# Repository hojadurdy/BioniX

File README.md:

### BioniX
Controller board for a prototype robotic prosthetic hand. 

#Features

- 5 servo motors. 1 for each finger.
- 2 servo motors for wrist gimbal.
- Onboard accelerometer and gyro.
- nRF805 Bleetooth SoC to communicate with mobile app.
- 600mA Li-Ion battery charging.
- 3.3V@1A Buck-Boost converter for EMG sensor and for the rest of the board.
- 6V@4A Boost converter for servos.

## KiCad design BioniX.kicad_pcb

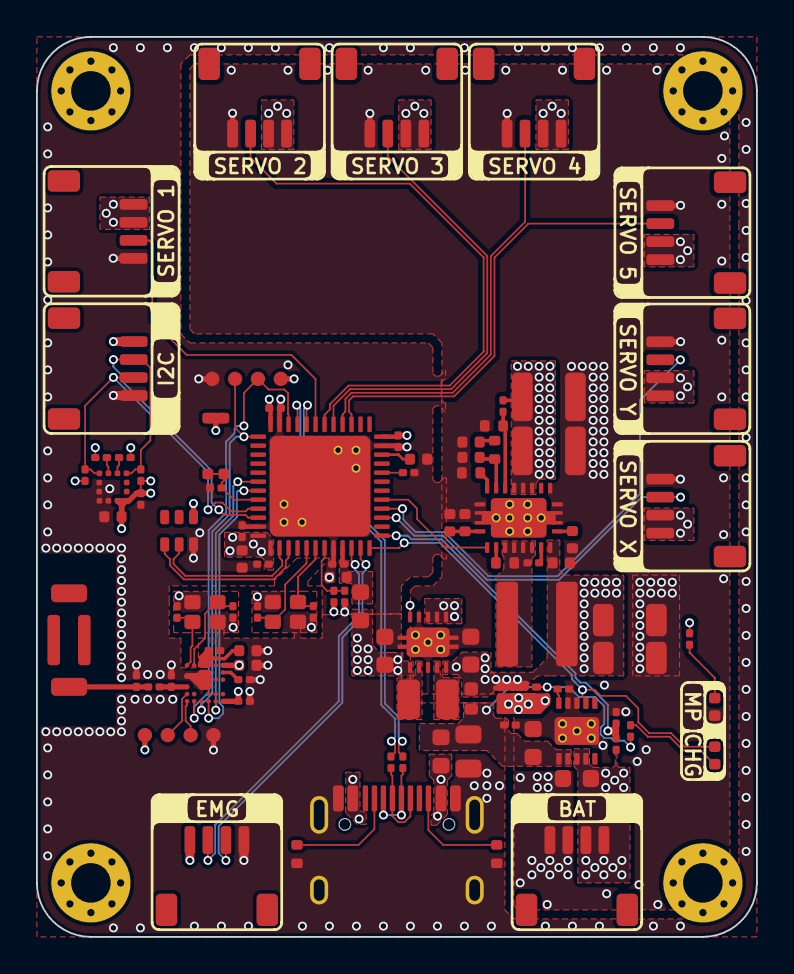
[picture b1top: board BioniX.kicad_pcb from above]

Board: 4 copper layers, 40.0 x 50.0 mm, 97 parts (0 on the bottom side), 64 nets.

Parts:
ANT1: 2450AT42B100; 2450AT42B100E
C1: 10uF; C_0805_2012Metric
C10, C60: 10uF; C_0402_1005Metric
C11, C12, C13, C14, C15, C18, C22, C24, C28, C52, C61: 100nF; C_0201_0603Metric
C16, C23, C54, C55: 1uF; C_0402_1005Metric
C17, C27: 2.2uF; C_0402_1005Metric
C19, C20, C21, C110: 18pF; C_0201_0603Metric
C25, C26: TBD; C_0201_0603Metric
C30, C31, C40: 10uF; C_0603_1608Metric
C41: 22uF; C_0603_1608Metric
C50, C51: 10uF; C_1206_3216Metric
C53: 100nF; C_0402_1005Metric
C56: 8.2nF; C_0402_1005Metric
C57: 560pF; C_0402_1005Metric
C58: 30pF; C_0402_1005Metric
C59, C510: 47uF; C_1210_3225Metric
D2: CCS15S30; CST2C
D3: APA102-2020
D30: STAT; LED_0402_1005Metric
D50: MOTOR_PWR; LED_0402_1005Metric
F1: 1A; Fuse_0603_1608Metric
FB1: 100@100MHz; L_0603_1608Metric
H1, H2, H3, H4: MountingHole; MountingHole_2.2mm_M2_Pad_Via
J1: USB-C; USB2.0_Type-C_Connector
J3: BAT; JST_SH_SM04B-SRSS-TB_1x04-1MP_P1.00mm_Horizontal
J4: EMG; JST_SH_SM04B-SRSS-TB_1x04-1MP_P1.00mm_Horizontal
J5: I2C; JST_SH_SM04B-SRSS-TB_1x04-1MP_P1.00mm_Horizontal
J6: Servo_X; JST_SH_SM04B-SRSS-TB_1x04-1MP_P1.00mm_Horizontal
J7: Servo_Y; JST_SH_SM04B-SRSS-TB_1x04-1MP_P1.00mm_Horizontal
J8, J9: SWD; SWD_Pogo_Pad
J10: Servo_1; JST_SH_SM04B-SRSS-TB_1x04-1MP_P1.00mm_Horizontal
J11: Servo_2; JST_SH_SM04B-SRSS-TB_1x04-1MP_P1.00mm_Horizontal
J12: Servo_3; JST_SH_SM04B-SRSS-TB_1x04-1MP_P1.00mm_Horizontal
J13: Servo_4; JST_SH_SM04B-SRSS-TB_1x04-1MP_P1.00mm_Horizontal
J14: Servo_5; JST_SH_SM04B-SRSS-TB_1x04-1MP_P1.00mm_Horizontal
L2: TBD; L_0201_0603Metric
L4: 1.5uH; L_1008_2520Metric
L5: 800nH; L_Coilcraft_XAL5030
Q1: SSM6J505NU; UDFN2020-6
R1, R2: 10; R_0201_0603Metric
R3, R4: 5.1K; R_0402_1005Metric
R5, R32, R33: 100K; R_0201_0603Metric
R10, R11, R12, R60, R61, R62, R63: 10K; R_0201_0603Metric
R30: 2.2K; R_0201_0603Metric
R31: 1.96K; R_0201_0603Metric
R50: 261K; R_0402_1005Metric
R51: 105K; R_0402_1005Metric
R52: 44.2K; R_0402_1005Metric
R53: 470K; R_0201_0603Metric
R54: 118K; R_0402_1005Metric
R55: 4.7K; R_0201_0603Metric
SW1: BOOT0; MicroSwitch
U1: STM32F411CEU6; QFN-48-1EP_7x7mm_P0.5mm_EP5.6x5.6mm
U2: nRF52805-CAAA; NRF52805-CAAA
U3: MCP73113-16SI; DFN-10-1EP_3x3mm_P0.5mm_EP1.55x2.48mm
U4: TPS63001DRC; Texas_VSON-10_3x3mm_P0.5mm
U5: TPS61088RHL; Texas_VQFN-RHL-20
U6: LIS2DW12TR; LGA-12_2x2mm_P0.5mm
Y1: 25MHz; Crystal_SMD_2016-4Pin_2.0x1.6mm
Y2: 32MHz; Crystal_SMD_2016-4Pin_2.0x1.6mm

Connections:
3.3V: C10.1, C11.1, C12.1, C13.1, C14.1, C27.1, C28.1, C41.1, C60.1, C61.1, D3.4 (VDD), FB1.2, J4.1 (VCC), J5.1 (VCC), J8.1 (VCC), J9.1 (VCC), R12.2, R60.2, R61.2, R62.2, R63.2, SW1.2, U1.1 (VBAT), U1.24 (VDD), U1.36 (VDD), U1.48 (VDD), U2.A6 (VDD), U2.G6 (VDD), U4.1 (VOUT), U4.10 (FB), U6.9 (VDD), U6.10 (VDD_IO)
6V: C59.1, C510.1, J6.1, J6.2, J7.1, J7.2, J10.1, J10.2, J11.1, J11.2, J12.1, J12.2, J13.1, J13.2, J14.1, J14.2, R53.1, R55.2, U5.14 (VOUT), U5.15 (VOUT), U5.16 (VOUT)
+3.3VA: C15.1, C16.1, FB1.1, U1.9 (VDDA)
BAT_STAT: D30.1 (K), U1.12 (PA2), U3.7 (STAT)
BAT_VOLT: R32.1, R33.2, U1.13 (PA3)
BOOST_EN: U1.17 (PA7), U5.2 (EN)
BOOT0: R10.2, SW1.1, U1.44 (BOOT0)
BT_1: J9.2 (DIO), U1.34 (PA13), U2.G2 (P0.21/NRESET)
BT_2: J9.3 (CLK), U1.37 (PA14), U2.G3 (P0.18)
BT_RX: U1.42 (PB6), U2.G5 (P0.12)
BT_SWCLK: J8.3 (CLK), U2.G1 (SWCLK)
BT_SWDIO: J8.2 (DIO), U2.F1 (SWDIO)
BT_TX: U1.43 (PB7), U2.G4 (P0.16)
CKI: D3.2 (CKI), U1.2 (PC13)
D+: R2.2, U1.33 (PA12)
D-: R1.2, U1.32 (PA11)
EMG_1: J4.2 (SIG1), U1.10 (PA0)
EMG_2: J4.3 (SIG2), U1.11 (PA1)
GND: C1.2, C10.2, C11.2, C12.2, C13.2, C14.2, C15.2, C16.2, C17.2, C18.2, C19.2, C20.1, C21.1, C22.2, C23.2, C24.2, C25.2, C26.2, C27.2, C28.2, C30.2, C31.2, C40.2, C41.2, C50.2, C51.2, C53.2, C54.2, C55.2, C56.2, C57.2, C58.2, C59.2, C60.2, C61.2, C110.2, C510.2, D3.3 (GND), D50.1 (K), J1.A1 (GND), J1.B1 (GND), J1.S1 (SHIELD), J3.1 (BAT-), J3.2 (BAT-), J4.4 (GND), J5.4 (GND), J6.4, J7.4, J8.4 (GND), J9.4 (GND), J10.4, J11.4, J12.4, J13.4, J14.4, R3.2, R4.2, R5.1, R10.1, R11.1, R31.1, R33.1, R51.2, R54.2, U1.8 (VSSA), U1.23 (VSS), U1.35 (VSS), U1.47 (VSS), U1.49 (VSS), U2.B3 (VSS), U2.B4 (VSS), U2.C1 (VSS), U2.D3 (VSS), U2.D4 (VSS), U2.E3 (VSS), U2.E4 (VSS), U3.8 (VSS), U3.9 (VSS), U3.11 (EP), U4.3 (PGND), U4.9 (GND), U4.11 (PGND), U5.11 (NC), U5.12 (NC), U5.20 (AGND), U5.21 (PGND), U6.5 (NC), U6.6 (GND), U6.7 (RES), U6.8 (GND), Y1.2, Y1.4, Y2.2, Y2.4
NRST: C18.1, R12.1, U1.7 (NRST)
unnamed: ANT1.1 (FEED), C26.1, L2.1
unnamed: C17.1, U1.22 (VCAP1)
unnamed: C19.1, U1.5 (OSC-IN/PH0), Y1.3
unnamed: C20.2, U2.A1 (XC1), Y2.3
unnamed: C21.2, U2.A2 (XC2), Y2.1
unnamed: C22.1, U2.B6 (DEC1)
unnamed: C23.1, C24.1, U2.A3 (DEC2), U2.A4 (DEC4)
unnamed: C25.1, L2.2, U2.E1 (ANT)
unnamed: C52.1, L5.2, R50.1, U5.4 (SW), U5.5 (SW), U5.6 (SW), U5.7 (SW)
unnamed: C52.2, U5.8 (BOOT)
unnamed: C54.1, C55.1, U5.1 (VCC)
unnamed: C56.1, U5.10 (SS)
unnamed: C57.1, R52.2
unnamed: C58.1, R52.1, U5.18 (COMP)
unnamed: C110.1, U1.6 (OSC-OUT/PH1), Y1.1
unnamed: D30.2 (A), R30.1
unnamed: D50.2 (A), R55.1
unnamed: F1.1, J1.A4 (VUSB), J1.B4 (VUSB)
unnamed: J1.A5 (CC1), R3.1
unnamed: J1.A6 (D+), J1.B6 (D+), R2.1
unnamed: J1.A7 (D-), J1.B7 (D-), R1.1
unnamed: J1.B5 (CC2), R4.1
unnamed: L4.1, U4.4 (L1)
unnamed: L4.2, U4.2 (L2)
unnamed: R11.2, U1.20 (PB2)
unnamed: R31.2, U3.10 (PROG)
unnamed: R50.2, U5.3 (FSW)
unnamed: R51.1, U5.19 (ILIM)
unnamed: R53.2, R54.1, U5.17 (FB)
unnamed: R60.1, U6.3 (SDO/SAO)
unnamed: R61.1, U6.2 (CS)
SCL: J5.3 (SCL), R63.1, U1.45 (PB8), U6.4 (SDA/SDI/SDO)
SDA: J5.2 (SDA), R62.1, U1.46 (PB9), U6.1 (SCL/SPC)
SDI: D3.1 (SDI), U1.3 (PC14)
SERVO_1: J10.3, U1.31 (PA10)
SERVO_2: J11.3, U1.30 (PA9)
SERVO_3: J12.3, U1.29 (PA8)
SERVO_4: J13.3, U1.28 (PB15)
SERVO_5: J14.3, U1.27 (PB14)
SERVO_X: J6.3, U1.15 (PA5)
SERVO_Y: J7.3, U1.16 (PA6)
VBAT: C31.1, J3.3 (BAT+), J3.4 (BAT+), Q1.1 (D), Q1.2 (D), Q1.5 (D), Q1.6 (D), Q1.7 (D), R32.2, U3.3 (VBAT), U3.4 (VBAT)
VBUS: C40.1, C50.1, C51.1, C53.1, D2.1 (K), L5.1, Q1.4 (S), Q1.8 (S), U4.5 (VIN), U4.6 (EN), U4.7 (PS/SYNC), U4.8 (VINA), U5.9 (VIN)
VUSB: C1.1, C30.1, D2.2 (A), F1.2, Q1.3 (G), R5.2, R30.2, U3.1 (VDD), U3.2 (VDD)
